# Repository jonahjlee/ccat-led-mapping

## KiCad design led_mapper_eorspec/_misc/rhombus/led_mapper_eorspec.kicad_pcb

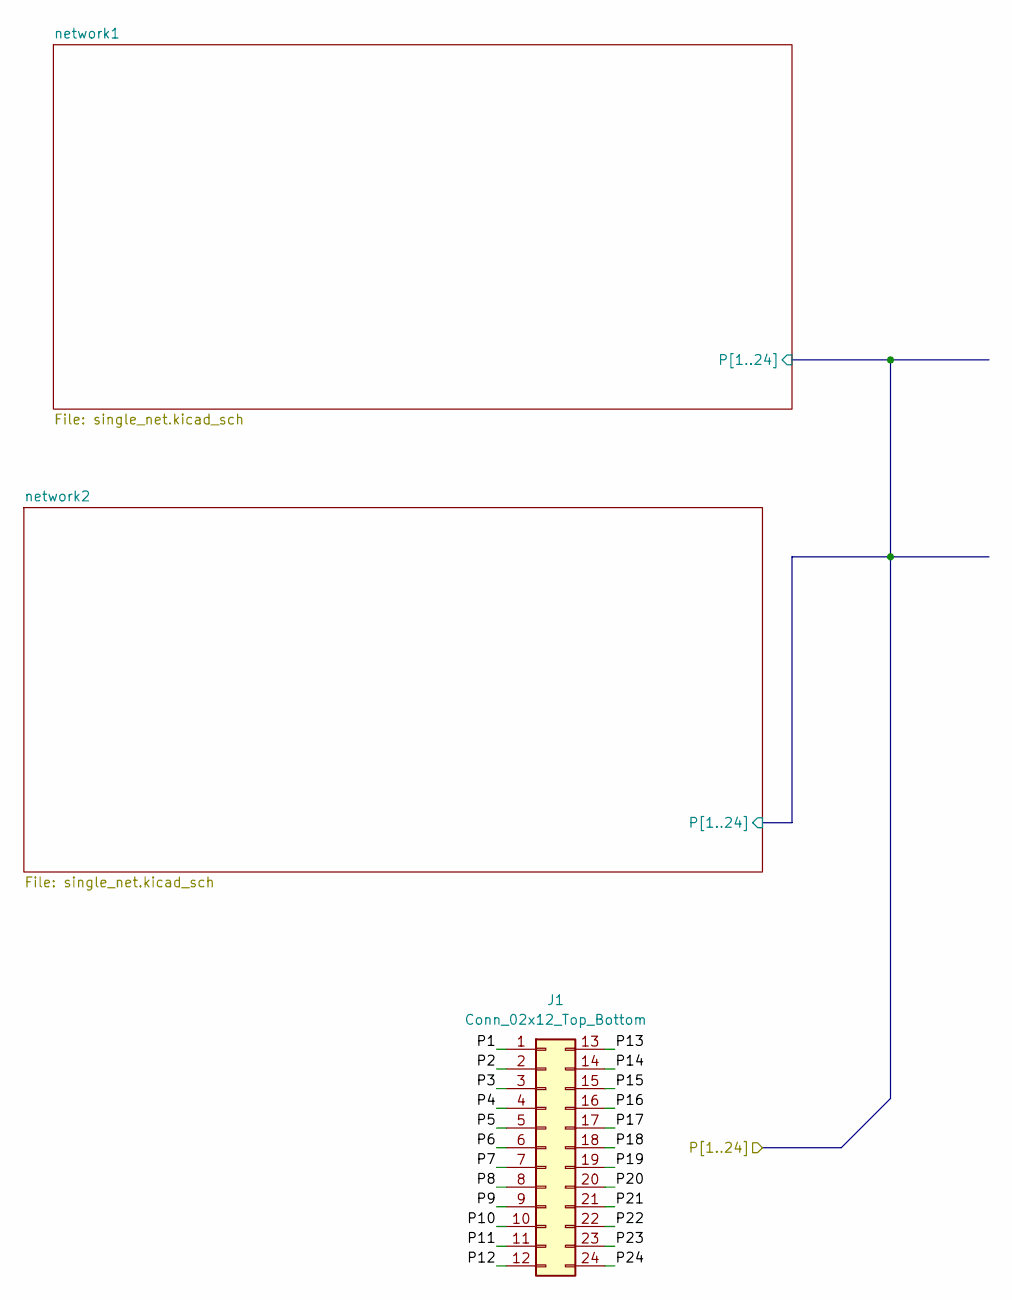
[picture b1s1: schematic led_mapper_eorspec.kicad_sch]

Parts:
J1: Conn_02x12_Top_Bottom; PinSocket_2x12_P2.54mm_Vertical_SMD_custom; LCSC Part # C19268781

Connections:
/P1: J1.1; also elsewhere on the board
/P2: J1.2; also elsewhere on the board
/P3: J1.3; also elsewhere on the board
/P4: J1.4; also elsewhere on the board
/P5: J1.5; also elsewhere on the board
/P6: J1.6; also elsewhere on the board
/P7: J1.7; also elsewhere on the board
/P8: J1.8; also elsewhere on the board
/P9: J1.9; also elsewhere on the board
/P10: J1.10; also elsewhere on the board
/P11: J1.11; also elsewhere on the board
/P12: J1.12; also elsewhere on the board
/P13: J1.13; also elsewhere on the board
/P14: J1.14; also elsewhere on the board
/P15: J1.15; also elsewhere on the board
/P16: J1.16; also elsewhere on the board
/P17: J1.17; also elsewhere on the board
/P18: J1.18; also elsewhere on the board
/P19: J1.19; also elsewhere on the board
/P20: J1.20; also elsewhere on the board
/P21: J1.21; also elsewhere on the board
/P22: J1.22; also elsewhere on the board
/P23: J1.23; also elsewhere on the board
/P24: J1.24; also elsewhere on the board

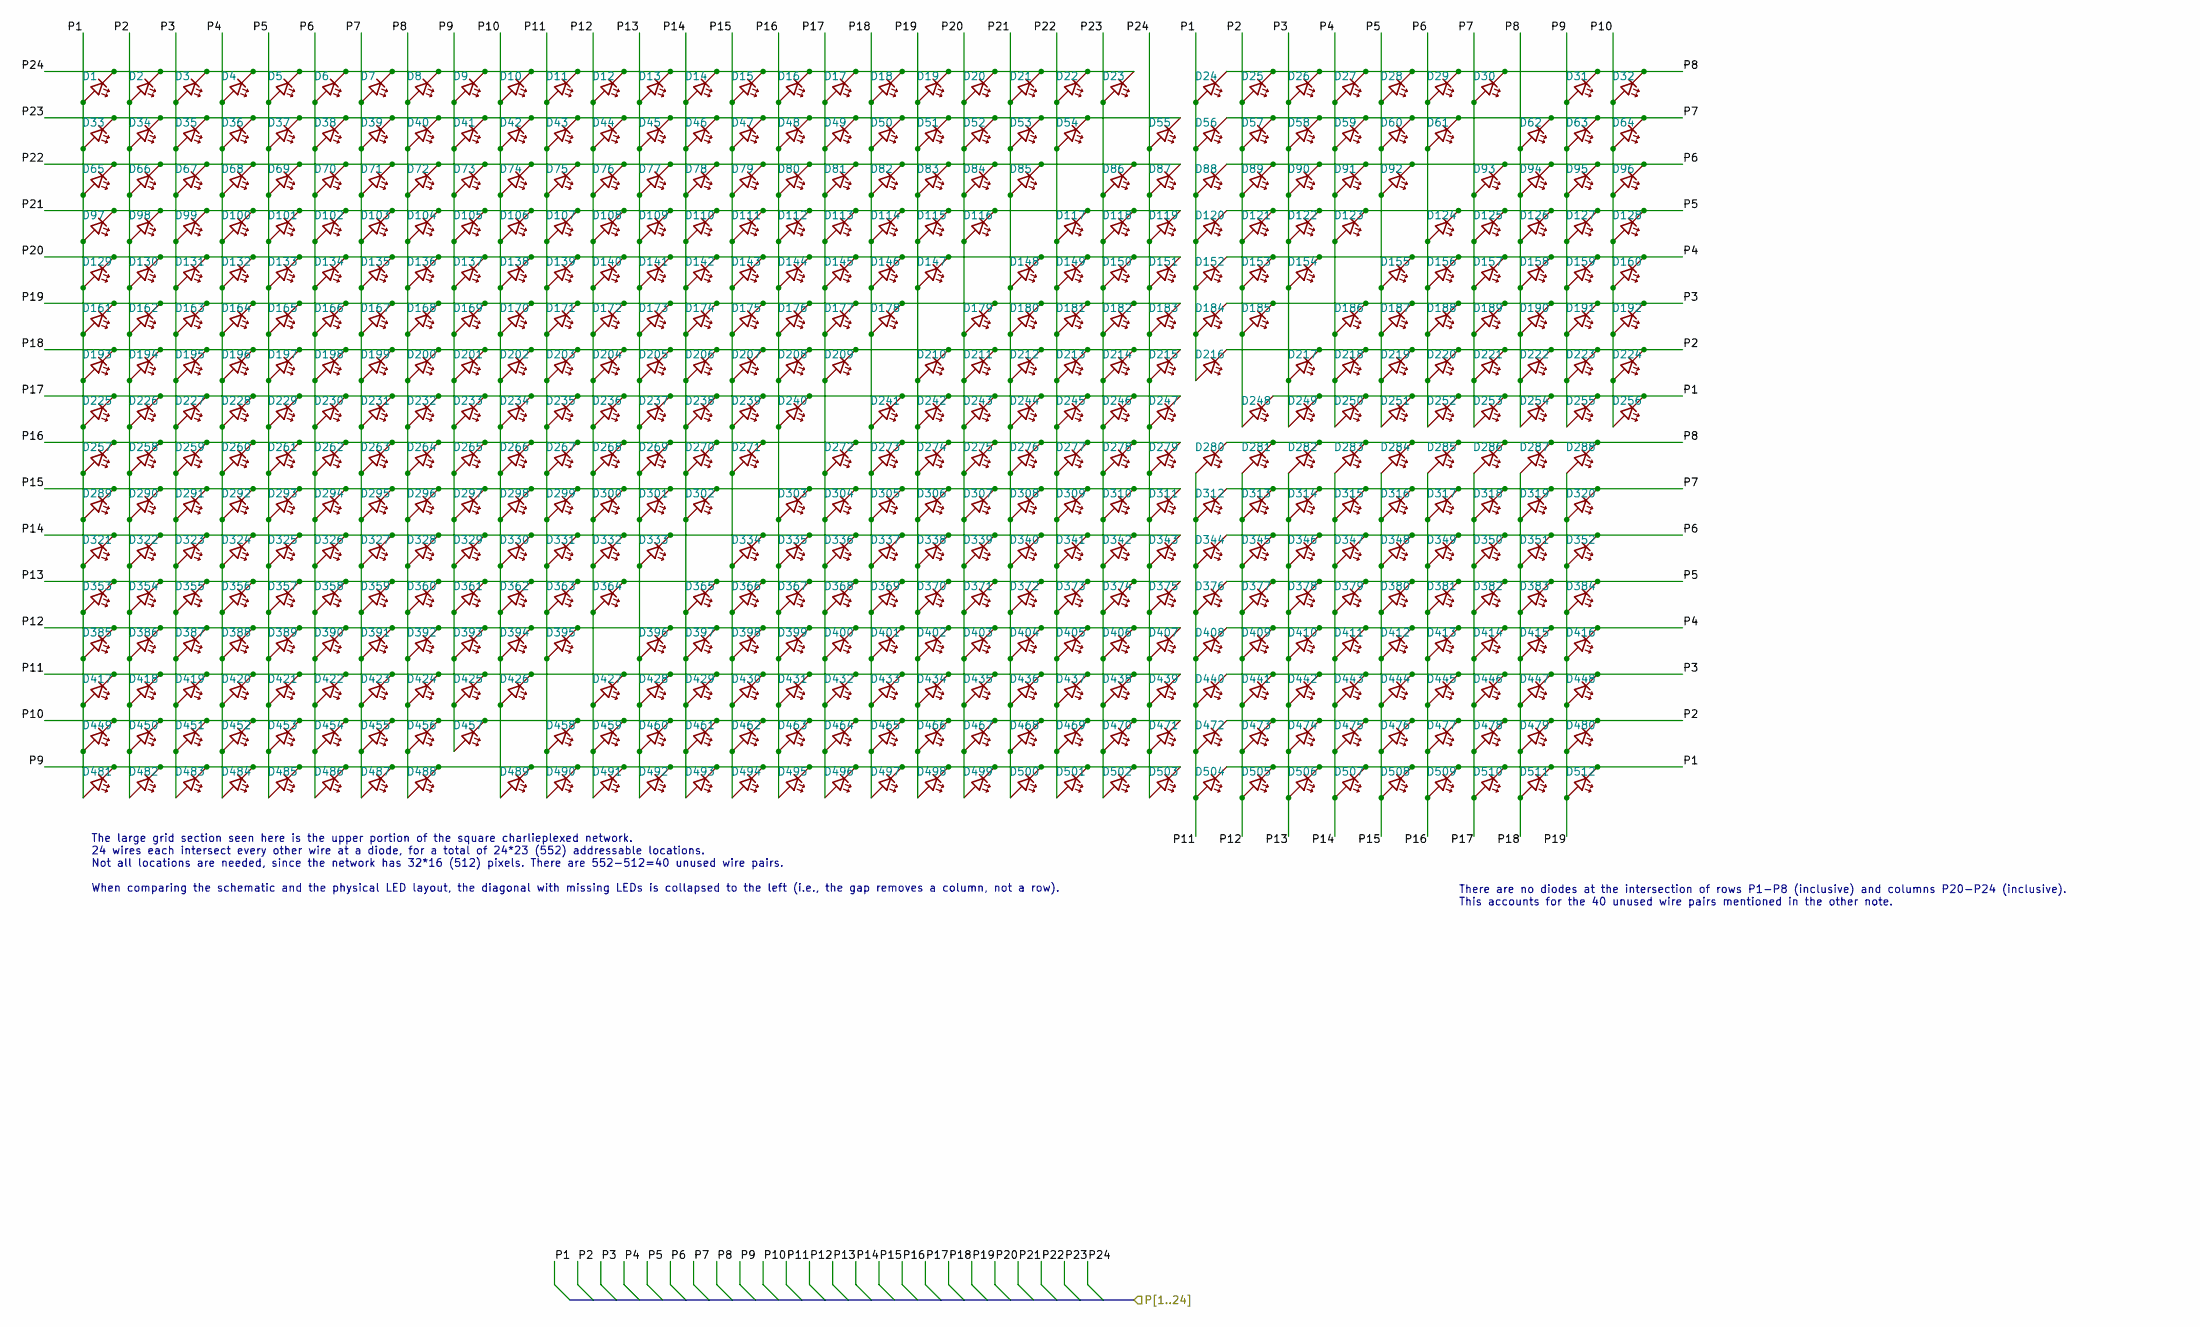
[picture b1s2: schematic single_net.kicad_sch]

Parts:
D1, D2, D3, D4, D5, D6, D7, D8, D9, D10, D11, D12, D13, D14, D15, D16, D17, D18, D19, D20, D21, D22, D23, D24, D25, D26, D27, D28, D29, D30, D31, D32, D33, D34, D35, D36, D37, D38, D39, D40, D41, D42, D43, D44, D45, D46, D47, D48, D49, D50, D51, D52, D53, D54, D55, D56, D57, D58, D59, D60, D61, D62, D63, D64, D65, D66, D67, D68, D69, D70, D71, D72, D73, D74, D75, D76, D77, D78, D79, D80, D81, D82, D83, D84, D85, D86, D87, D88, D89, D90, D91, D92, D93, D94, D95, D96, D97, D98, D99, D100, D101, D102, D103, D104, D105, D106, D107, D108, D109, D110, D111, D112, D113, D114, D115, D116, D117, D118, D119, D120, D121, D122, D123, D124, D125, D126, D127, D128, D129, D130, D131, D132, D133, D134, D135, D136, D137, D138, D139, D140, D141, D142, D143, D144, D145, D146, D147, D148, D149, D150, D151, D152, D153, D154, D155, D156, D157, D158, D159, D160, D161, D162, D163, D164, D165, D166, D167, D168, D169, D170, D171, D172, D173, D174, D175, D176, D177, D178, D179, D180, D181, D182, D183, D184, D185, D186, D187, D188, D189, D190, D191, D192, D193, D194, D195, D196, D197, D198, D199, D200, D201, D202, D203, D204, D205, D206, D207, D208, D209, D210, D211, D212, D213, D214, D215, D216, D217, D218, D219, D220, D221, D222, D223, D224, D225, D226, D227, D228, D229, D230, D231, D232, D233, D234, D235, D236, D237, D238, D239, D240, D241, D242, D243, D244, D245, D246, D247, D248, D249, D250, D251, D252, D253, D254, D255, D256, D257, D258, D259, D260, D261, D262, D263, D264, D265, D266, D267, D268, D269, D270, D271, D272, D273, D274, D275, D276, D277, D278, D279, D280, D281, D282, D283, D284, D285, D286, D287, D288, D289, D290, D291, D292, D293, D294, D295, D296, D297, D298, D299, D300, D301, D302, D303, D304, D305, D306, D307, D308, D309, D310, D311, D312, D313, D314, D315, D316, D317, D318, D319, D320, D321, D322, D323, D324, D325, D326, D327, D328, D329, D330, D331, D332, D333, D334, D335, D336, D337, D338, D339, D340, D341, D342, D343, D344, D345, D346, D347, D348, D349, D350, D351, D352, D353, D354, D355, D356, D357, D358, D359, D360, D361, D362, D363, D364, D365, D366, D367, D368, D369, D370, D371, D372, D373, D374, D375, D376, D377, D378, D379, D380, D381, D382, D383, D384, D385, D386, D387, D388, D389, D390, D391, D392, D393, D394, D395, D396, D397, D398, D399, D400, D401, D402, D403, D404, D405, D406, D407, D408, D409, D410, D411, D412, D413, D414, D415, D416, D417, D418, D419, D420, D421, D422, D423, D424, D425, D426, D427, D428, D429, D430, D431, D432, D433, D434, D435, D436, D437, D438, D439, D440, D441, D442, D443, D444, D445, D446, D447, D448, D449, D450, D451, D452, D453, D454, D455, D456, D457, D458, D459, D460, D461, D462, D463, D464, D465, D466, D467, D468, D469, D470, D471, D472, D473, D474, D475, D476, D477, D478, D479, D480, D481, D482, D483, D484, D485, D486, D487, D488, D489, D490, D491, D492, D493, D494, D495, D496, D497, D498, D499, D500, D501, D502, D503, D504, D505, D506, D507, D508, D509, D510, D511, D512: LED_45deg

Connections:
/P1: D1.2 (A), D24.2 (A), D33.2 (A), D56.2 (A), D65.2 (A), D88.2 (A), D97.2 (A), D120.2 (A), D129.2 (A), D152.2 (A), D161.2 (A), D184.2 (A), D193.2 (A), D216.2 (A), D225.2 (A), D248.1 (K), D249.1 (K), D250.1 (K), D251.1 (K), D252.1 (K), D253.1 (K), D254.1 (K), D255.1 (K), D256.1 (K), D257.2 (A), D289.2 (A), D321.2 (A), D353.2 (A), D385.2 (A), D417.2 (A), D449.2 (A), D481.2 (A), D504.1 (K), D505.1 (K), D506.1 (K), D507.1 (K), D508.1 (K), D509.1 (K), D510.1 (K), D511.1 (K), D512.1 (K); also elsewhere on the board
/P2: D2.2 (A), D25.2 (A), D34.2 (A), D57.2 (A), D66.2 (A), D89.2 (A), D98.2 (A), D121.2 (A), D130.2 (A), D153.2 (A), D162.2 (A), D185.2 (A), D194.2 (A), D216.1 (K), D217.1 (K), D218.1 (K), D219.1 (K), D220.1 (K), D221.1 (K), D222.1 (K), D223.1 (K), D224.1 (K), D226.2 (A), D248.2 (A), D258.2 (A), D290.2 (A), D322.2 (A), D354.2 (A), D386.2 (A), D418.2 (A), D450.2 (A), D472.1 (K), D473.1 (K), D474.1 (K), D475.1 (K), D476.1 (K), D477.1 (K), D478.1 (K), D479.1 (K), D480.1 (K), D482.2 (A); also elsewhere on the board
/P3: D3.2 (A), D26.2 (A), D35.2 (A), D58.2 (A), D67.2 (A), D90.2 (A), D99.2 (A), D122.2 (A), D131.2 (A), D154.2 (A), D163.2 (A), D184.1 (K), D185.1 (K), D186.1 (K), D187.1 (K), D188.1 (K), D189.1 (K), D190.1 (K), D191.1 (K), D192.1 (K), D195.2 (A), D217.2 (A), D227.2 (A), D249.2 (A), D259.2 (A), D291.2 (A), D323.2 (A), D355.2 (A), D387.2 (A), D419.2 (A), D440.1 (K), D441.1 (K), D442.1 (K), D443.1 (K), D444.1 (K), D445.1 (K), D446.1 (K), D447.1 (K), D448.1 (K), D451.2 (A), D483.2 (A); also elsewhere on the board
/P4: D4.2 (A), D27.2 (A), D36.2 (A), D59.2 (A), D68.2 (A), D91.2 (A), D100.2 (A), D123.2 (A), D132.2 (A), D152.1 (K), D153.1 (K), D154.1 (K), D155.1 (K), D156.1 (K), D157.1 (K), D158.1 (K), D159.1 (K), D160.1 (K), D164.2 (A), D186.2 (A), D196.2 (A), D218.2 (A), D228.2 (A), D250.2 (A), D260.2 (A), D292.2 (A), D324.2 (A), D356.2 (A), D388.2 (A), D408.1 (K), D409.1 (K), D410.1 (K), D411.1 (K), D412.1 (K), D413.1 (K), D414.1 (K), D415.1 (K), D416.1 (K), D420.2 (A), D452.2 (A), D484.2 (A); also elsewhere on the board
/P5: D5.2 (A), D28.2 (A), D37.2 (A), D60.2 (A), D69.2 (A), D92.2 (A), D101.2 (A), D120.1 (K), D121.1 (K), D122.1 (K), D123.1 (K), D124.1 (K), D125.1 (K), D126.1 (K), D127.1 (K), D128.1 (K), D133.2 (A), D155.2 (A), D165.2 (A), D187.2 (A), D197.2 (A), D219.2 (A), D229.2 (A), D251.2 (A), D261.2 (A), D293.2 (A), D325.2 (A), D357.2 (A), D376.1 (K), D377.1 (K), D378.1 (K), D379.1 (K), D380.1 (K), D381.1 (K), D382.1 (K), D383.1 (K), D384.1 (K), D389.2 (A), D421.2 (A), D453.2 (A), D485.2 (A); also elsewhere on the board
/P6: D6.2 (A), D29.2 (A), D38.2 (A), D61.2 (A), D70.2 (A), D88.1 (K), D89.1 (K), D90.1 (K), D91.1 (K), D92.1 (K), D93.1 (K), D94.1 (K), D95.1 (K), D96.1 (K), D102.2 (A), D124.2 (A), D134.2 (A), D156.2 (A), D166.2 (A), D188.2 (A), D198.2 (A), D220.2 (A), D230.2 (A), D252.2 (A), D262.2 (A), D294.2 (A), D326.2 (A), D344.1 (K), D345.1 (K), D346.1 (K), D347.1 (K), D348.1 (K), D349.1 (K), D350.1 (K), D351.1 (K), D352.1 (K), D358.2 (A), D390.2 (A), D422.2 (A), D454.2 (A), D486.2 (A); also elsewhere on the board
/P7: D7.2 (A), D30.2 (A), D39.2 (A), D56.1 (K), D57.1 (K), D58.1 (K), D59.1 (K), D60.1 (K), D61.1 (K), D62.1 (K), D63.1 (K), D64.1 (K), D71.2 (A), D93.2 (A), D103.2 (A), D125.2 (A), D135.2 (A), D157.2 (A), D167.2 (A), D189.2 (A), D199.2 (A), D221.2 (A), D231.2 (A), D253.2 (A), D263.2 (A), D295.2 (A), D312.1 (K), D313.1 (K), D314.1 (K), D315.1 (K), D316.1 (K), D317.1 (K), D318.1 (K), D319.1 (K), D320.1 (K), D327.2 (A), D359.2 (A), D391.2 (A), D423.2 (A), D455.2 (A), D487.2 (A); also elsewhere on the board
/P8: D8.2 (A), D24.1 (K), D25.1 (K), D26.1 (K), D27.1 (K), D28.1 (K), D29.1 (K), D30.1 (K), D31.1 (K), D32.1 (K), D40.2 (A), D62.2 (A), D72.2 (A), D94.2 (A), D104.2 (A), D126.2 (A), D136.2 (A), D158.2 (A), D168.2 (A), D190.2 (A), D200.2 (A), D222.2 (A), D232.2 (A), D254.2 (A), D264.2 (A), D280.1 (K), D281.1 (K), D282.1 (K), D283.1 (K), D284.1 (K), D285.1 (K), D286.1 (K), D287.1 (K), D288.1 (K), D296.2 (A), D328.2 (A), D360.2 (A), D392.2 (A), D424.2 (A), D456.2 (A), D488.2 (A); also elsewhere on the board
/P9: D9.2 (A), D31.2 (A), D41.2 (A), D63.2 (A), D73.2 (A), D95.2 (A), D105.2 (A), D127.2 (A), D137.2 (A), D159.2 (A), D169.2 (A), D191.2 (A), D201.2 (A), D223.2 (A), D233.2 (A), D255.2 (A), D265.2 (A), D297.2 (A), D329.2 (A), D361.2 (A), D393.2 (A), D425.2 (A), D457.2 (A), D481.1 (K), D482.1 (K), D483.1 (K), D484.1 (K), D485.1 (K), D486.1 (K), D487.1 (K), D488.1 (K), D489.1 (K), D490.1 (K), D491.1 (K), D492.1 (K), D493.1 (K), D494.1 (K), D495.1 (K), D496.1 (K), D497.1 (K), D498.1 (K), D499.1 (K), D500.1 (K), D501.1 (K), D502.1 (K), D503.1 (K); also elsewhere on the board
/P10: D10.2 (A), D32.2 (A), D42.2 (A), D64.2 (A), D74.2 (A), D96.2 (A), D106.2 (A), D128.2 (A), D138.2 (A), D160.2 (A), D170.2 (A), D192.2 (A), D202.2 (A), D224.2 (A), D234.2 (A), D256.2 (A), D266.2 (A), D298.2 (A), D330.2 (A), D362.2 (A), D394.2 (A), D426.2 (A), D449.1 (K), D450.1 (K), D451.1 (K), D452.1 (K), D453.1 (K), D454.1 (K), D455.1 (K), D456.1 (K), D457.1 (K), D458.1 (K), D459.1 (K), D460.1 (K), D461.1 (K), D462.1 (K), D463.1 (K), D464.1 (K), D465.1 (K), D466.1 (K), D467.1 (K), D468.1 (K), D469.1 (K), D470.1 (K), D471.1 (K), D489.2 (A); also elsewhere on the board
/P11: D11.2 (A), D43.2 (A), D75.2 (A), D107.2 (A), D139.2 (A), D171.2 (A), D203.2 (A), D235.2 (A), D267.2 (A), D280.2 (A), D299.2 (A), D312.2 (A), D331.2 (A), D344.2 (A), D363.2 (A), D376.2 (A), D395.2 (A), D408.2 (A), D417.1 (K), D418.1 (K), D419.1 (K), D420.1 (K), D421.1 (K), D422.1 (K), D423.1 (K), D424.1 (K), D425.1 (K), D426.1 (K), D427.1 (K), D428.1 (K), D429.1 (K), D430.1 (K), D431.1 (K), D432.1 (K), D433.1 (K), D434.1 (K), D435.1 (K), D436.1 (K), D437.1 (K), D438.1 (K), D439.1 (K), D440.2 (A), D458.2 (A), D472.2 (A), D490.2 (A), D504.2 (A); also elsewhere on the board
/P12: D12.2 (A), D44.2 (A), D76.2 (A), D108.2 (A), D140.2 (A), D172.2 (A), D204.2 (A), D236.2 (A), D268.2 (A), D281.2 (A), D300.2 (A), D313.2 (A), D332.2 (A), D345.2 (A), D364.2 (A), D377.2 (A), D385.1 (K), D386.1 (K), D387.1 (K), D388.1 (K), D389.1 (K), D390.1 (K), D391.1 (K), D392.1 (K), D393.1 (K), D394.1 (K), D395.1 (K), D396.1 (K), D397.1 (K), D398.1 (K), D399.1 (K), D400.1 (K), D401.1 (K), D402.1 (K), D403.1 (K), D404.1 (K), D405.1 (K), D406.1 (K), D407.1 (K), D409.2 (A), D427.2 (A), D441.2 (A), D459.2 (A), D473.2 (A), D491.2 (A), D505.2 (A); also elsewhere on the board
/P13: D13.2 (A), D45.2 (A), D77.2 (A), D109.2 (A), D141.2 (A), D173.2 (A), D205.2 (A), D237.2 (A), D269.2 (A), D282.2 (A), D301.2 (A), D314.2 (A), D333.2 (A), D346.2 (A), D353.1 (K), D354.1 (K), D355.1 (K), D356.1 (K), D357.1 (K), D358.1 (K), D359.1 (K), D360.1 (K), D361.1 (K), D362.1 (K), D363.1 (K), D364.1 (K), D365.1 (K), D366.1 (K), D367.1 (K), D368.1 (K), D369.1 (K), D370.1 (K), D371.1 (K), D372.1 (K), D373.1 (K), D374.1 (K), D375.1 (K), D378.2 (A), D396.2 (A), D410.2 (A), D428.2 (A), D442.2 (A), D460.2 (A), D474.2 (A), D492.2 (A), D506.2 (A); also elsewhere on the board
/P14: D14.2 (A), D46.2 (A), D78.2 (A), D110.2 (A), D142.2 (A), D174.2 (A), D206.2 (A), D238.2 (A), D270.2 (A), D283.2 (A), D302.2 (A), D315.2 (A), D321.1 (K), D322.1 (K), D323.1 (K), D324.1 (K), D325.1 (K), D326.1 (K), D327.1 (K), D328.1 (K), D329.1 (K), D330.1 (K), D331.1 (K), D332.1 (K), D333.1 (K), D334.1 (K), D335.1 (K), D336.1 (K), D337.1 (K), D338.1 (K), D339.1 (K), D340.1 (K), D341.1 (K), D342.1 (K), D343.1 (K), D347.2 (A), D365.2 (A), D379.2 (A), D397.2 (A), D411.2 (A), D429.2 (A), D443.2 (A), D461.2 (A), D475.2 (A), D493.2 (A), D507.2 (A); also elsewhere on the board
/P15: D15.2 (A), D47.2 (A), D79.2 (A), D111.2 (A), D143.2 (A), D175.2 (A), D207.2 (A), D239.2 (A), D271.2 (A), D284.2 (A), D289.1 (K), D290.1 (K), D291.1 (K), D292.1 (K), D293.1 (K), D294.1 (K), D295.1 (K), D296.1 (K), D297.1 (K), D298.1 (K), D299.1 (K), D300.1 (K), D301.1 (K), D302.1 (K), D303.1 (K), D304.1 (K), D305.1 (K), D306.1 (K), D307.1 (K), D308.1 (K), D309.1 (K), D310.1 (K), D311.1 (K), D316.2 (A), D334.2 (A), D348.2 (A), D366.2 (A), D380.2 (A), D398.2 (A), D412.2 (A), D430.2 (A), D444.2 (A), D462.2 (A), D476.2 (A), D494.2 (A), D508.2 (A); also elsewhere on the board
/P16: D16.2 (A), D48.2 (A), D80.2 (A), D112.2 (A), D144.2 (A), D176.2 (A), D208.2 (A), D240.2 (A), D257.1 (K), D258.1 (K), D259.1 (K), D260.1 (K), D261.1 (K), D262.1 (K), D263.1 (K), D264.1 (K), D265.1 (K), D266.1 (K), D267.1 (K), D268.1 (K), D269.1 (K), D270.1 (K), D271.1 (K), D272.1 (K), D273.1 (K), D274.1 (K), D275.1 (K), D276.1 (K), D277.1 (K), D278.1 (K), D279.1 (K), D285.2 (A), D303.2 (A), D317.2 (A), D335.2 (A), D349.2 (A), D367.2 (A), D381.2 (A), D399.2 (A), D413.2 (A), D431.2 (A), D445.2 (A), D463.2 (A), D477.2 (A), D495.2 (A), D509.2 (A); also elsewhere on the board
/P17: D17.2 (A), D49.2 (A), D81.2 (A), D113.2 (A), D145.2 (A), D177.2 (A), D209.2 (A), D225.1 (K), D226.1 (K), D227.1 (K), D228.1 (K), D229.1 (K), D230.1 (K), D231.1 (K), D232.1 (K), D233.1 (K), D234.1 (K), D235.1 (K), D236.1 (K), D237.1 (K), D238.1 (K), D239.1 (K), D240.1 (K), D241.1 (K), D242.1 (K), D243.1 (K), D244.1 (K), D245.1 (K), D246.1 (K), D247.1 (K), D272.2 (A), D286.2 (A), D304.2 (A), D318.2 (A), D336.2 (A), D350.2 (A), D368.2 (A), D382.2 (A), D400.2 (A), D414.2 (A), D432.2 (A), D446.2 (A), D464.2 (A), D478.2 (A), D496.2 (A), D510.2 (A); also elsewhere on the board
/P18: D18.2 (A), D50.2 (A), D82.2 (A), D114.2 (A), D146.2 (A), D178.2 (A), D193.1 (K), D194.1 (K), D195.1 (K), D196.1 (K), D197.1 (K), D198.1 (K), D199.1 (K), D200.1 (K), D201.1 (K), D202.1 (K), D203.1 (K), D204.1 (K), D205.1 (K), D206.1 (K), D207.1 (K), D208.1 (K), D209.1 (K), D210.1 (K), D211.1 (K), D212.1 (K), D213.1 (K), D214.1 (K), D215.1 (K), D241.2 (A), D273.2 (A), D287.2 (A), D305.2 (A), D319.2 (A), D337.2 (A), D351.2 (A), D369.2 (A), D383.2 (A), D401.2 (A), D415.2 (A), D433.2 (A), D447.2 (A), D465.2 (A), D479.2 (A), D497.2 (A), D511.2 (A); also elsewhere on the board
/P19: D19.2 (A), D51.2 (A), D83.2 (A), D115.2 (A), D147.2 (A), D161.1 (K), D162.1 (K), D163.1 (K), D164.1 (K), D165.1 (K), D166.1 (K), D167.1 (K), D168.1 (K), D169.1 (K), D170.1 (K), D171.1 (K), D172.1 (K), D173.1 (K), D174.1 (K), D175.1 (K), D176.1 (K), D177.1 (K), D178.1 (K), D179.1 (K), D180.1 (K), D181.1 (K), D182.1 (K), D183.1 (K), D210.2 (A), D242.2 (A), D274.2 (A), D288.2 (A), D306.2 (A), D320.2 (A), D338.2 (A), D352.2 (A), D370.2 (A), D384.2 (A), D402.2 (A), D416.2 (A), D434.2 (A), D448.2 (A), D466.2 (A), D480.2 (A), D498.2 (A), D512.2 (A); also elsewhere on the board
/P20: D20.2 (A), D52.2 (A), D84.2 (A), D116.2 (A), D129.1 (K), D130.1 (K), D131.1 (K), D132.1 (K), D133.1 (K), D134.1 (K), D135.1 (K), D136.1 (K), D137.1 (K), D138.1 (K), D139.1 (K), D140.1 (K), D141.1 (K), D142.1 (K), D143.1 (K), D144.1 (K), D145.1 (K), D146.1 (K), D147.1 (K), D148.1 (K), D149.1 (K), D150.1 (K), D151.1 (K), D179.2 (A), D211.2 (A), D243.2 (A), D275.2 (A), D307.2 (A), D339.2 (A), D371.2 (A), D403.2 (A), D435.2 (A), D467.2 (A), D499.2 (A); also elsewhere on the board
/P21: D21.2 (A), D53.2 (A), D85.2 (A), D97.1 (K), D98.1 (K), D99.1 (K), D100.1 (K), D101.1 (K), D102.1 (K), D103.1 (K), D104.1 (K), D105.1 (K), D106.1 (K), D107.1 (K), D108.1 (K), D109.1 (K), D110.1 (K), D111.1 (K), D112.1 (K), D113.1 (K), D114.1 (K), D115.1 (K), D116.1 (K), D117.1 (K), D118.1 (K), D119.1 (K), D148.2 (A), D180.2 (A), D212.2 (A), D244.2 (A), D276.2 (A), D308.2 (A), D340.2 (A), D372.2 (A), D404.2 (A), D436.2 (A), D468.2 (A), D500.2 (A); also elsewhere on the board
/P22: D22.2 (A), D54.2 (A), D65.1 (K), D66.1 (K), D67.1 (K), D68.1 (K), D69.1 (K), D70.1 (K), D71.1 (K), D72.1 (K), D73.1 (K), D74.1 (K), D75.1 (K), D76.1 (K), D77.1 (K), D78.1 (K), D79.1 (K), D80.1 (K), D81.1 (K), D82.1 (K), D83.1 (K), D84.1 (K), D85.1 (K), D86.1 (K), D87.1 (K), D117.2 (A), D149.2 (A), D181.2 (A), D213.2 (A), D245.2 (A), D277.2 (A), D309.2 (A), D341.2 (A), D373.2 (A), D405.2 (A), D437.2 (A), D469.2 (A), D501.2 (A); also elsewhere on the board
/P23: D23.2 (A), D33.1 (K), D34.1 (K), D35.1 (K), D36.1 (K), D37.1 (K), D38.1 (K), D39.1 (K), D40.1 (K), D41.1 (K), D42.1 (K), D43.1 (K), D44.1 (K), D45.1 (K), D46.1 (K), D47.1 (K), D48.1 (K), D49.1 (K), D50.1 (K), D51.1 (K), D52.1 (K), D53.1 (K), D54.1 (K), D55.1 (K), D86.2 (A), D118.2 (A), D150.2 (A), D182.2 (A), D214.2 (A), D246.2 (A), D278.2 (A), D310.2 (A), D342.2 (A), D374.2 (A), D406.2 (A), D438.2 (A), D470.2 (A), D502.2 (A); also elsewhere on the board
/P24: D1.1 (K), D2.1 (K), D3.1 (K), D4.1 (K), D5.1 (K), D6.1 (K), D7.1 (K), D8.1 (K), D9.1 (K), D10.1 (K), D11.1 (K), D12.1 (K), D13.1 (K), D14.1 (K), D15.1 (K), D16.1 (K), D17.1 (K), D18.1 (K), D19.1 (K), D20.1 (K), D21.1 (K), D22.1 (K), D23.1 (K), D55.2 (A), D87.2 (A), D119.2 (A), D151.2 (A), D183.2 (A), D215.2 (A), D247.2 (A), D279.2 (A), D311.2 (A), D343.2 (A), D375.2 (A), D407.2 (A), D439.2 (A), D471.2 (A), D503.2 (A); also elsewhere on the board

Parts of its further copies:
D513, D514, D515, D516, D517, D518, D519, D520, D521, D522, D523, D524, D525, D526, D527, D528, D529, D530, D531, D532, D533, D534, D535, D536, D537, D538, D539, D540, D541, D542, D543, D544, D545, D546, D547, D548, D549, D550, D551, D552, D553, D554, D555, D556, D557, D558, D559, D560, D561, D562, D563, D564, D565, D566, D567, D568, D569, D570, D571, D572, D573, D574, D575, D576, D577, D578, D579, D580, D581, D582, D583, D584, D585, D586, D587, D588, D589, D590, D591, D592, D593, D594, D595, D596, D597, D598, D599, D600, D601, D602, D603, D604, D605, D606, D607, D608, D609, D610, D611, D612, D613, D614, D615, D616, D617, D618, D619, D620, D621, D622, D623, D624, D625, D626, D627, D628, D629, D630, D631, D632, D633, D634, D635, D636, D637, D638, D639, D640, D641, D642, D643, D644, D645, D646, D647, D648, D649, D650, D651, D652, D653, D654, D655, D656, D657, D658, D659, D660, D661, D662, D663, D664, D665, D666, D667, D668, D669, D670, D671, D672, D673, D674, D675, D676, D677, D678, D679, D680, D681, D682, D683, D684, D685, D686, D687, D688, D689, D690, D691, D692, D693, D694, D695, D696, D697, D698, D699, D700, D701, D702, D703, D704, D705, D706, D707, D708, D709, D710, D711, D712, D713, D714, D715, D716, D717, D718, D719, D720, D721, D722, D723, D724, D725, D726, D727, D728, D729, D730, D731, D732, D733, D734, D735, D736, D737, D738, D739, D740, D741, D742, D743, D744, D745, D746, D747, D748, D749, D750, D751, D752, D753, D754, D755, D756, D757, D758, D759, D760, D761, D762, D763, D764, D765, D766, D767, D768, D769, D770, D771, D772, D773, D774, D775, D776, D777, D778, D779, D780, D781, D782, D783, D784, D785, D786, D787, D788, D789, D790, D791, D792, D793, D794, D795, D796, D797, D798, D799, D800, D801, D802, D803, D804, D805, D806, D807, D808, D809, D810, D811, D812, D813, D814, D815, D816, D817, D818, D819, D820, D821, D822, D823, D824, D825, D826, D827, D828, D829, D830, D831, D832, D833, D834, D835, D836, D837, D838, D839, D840, D841, D842, D843, D844, D845, D846, D847, D848, D849, D850, D851, D852, D853, D854, D855, D856, D857, D858, D859, D860, D861, D862, D863, D864, D865, D866, D867, D868, D869, D870, D871, D872, D873, D874, D875, D876, D877, D878, D879, D880, D881, D882, D883, D884, D885, D886, D887, D888, D889, D890, D891, D892, D893, D894, D895, D896, D897, D898, D899, D900, D901, D902, D903, D904, D905, D906, D907, D908, D909, D910, D911, D912, D913, D914, D915, D916, D917, D918, D919, D920, D921, D922, D923, D924, D925, D926, D927, D928, D929, D930, D931, D932, D933, D934, D935, D936, D937, D938, D939, D940, D941, D942, D943, D944, D945, D946, D947, D948, D949, D950, D951, D952, D953, D954, D955, D956, D957, D958, D959, D960, D961, D962, D963, D964, D965, D966, D967, D968, D969, D970, D971, D972, D973, D974, D975, D976, D977, D978, D979, D980, D981, D982, D983, D984, D985, D986, D987, D988, D989, D990, D991, D992, D993, D994, D995, D996, D997, D998, D999, D1000, D1001, D1002, D1003, D1004, D1005, D1006, D1007, D1008, D1009, D1010, D1011, D1012, D1013, D1014, D1015, D1016, D1017, D1018, D1019, D1020, D1021, D1022, D1023, D1024: LED_45deg

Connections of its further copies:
/P1: D513.2 (A), D536.2 (A), D545.2 (A), D568.2 (A), D577.2 (A), D600.2 (A), D609.2 (A), D632.2 (A), D641.2 (A), D664.2 (A), D673.2 (A), D696.2 (A), D705.2 (A), D728.2 (A), D737.2 (A), D760.1 (K), D761.1 (K), D762.1 (K), D763.1 (K), D764.1 (K), D765.1 (K), D766.1 (K), D767.1 (K), D768.1 (K), D769.2 (A), D801.2 (A), D833.2 (A), D865.2 (A), D897.2 (A), D929.2 (A), D961.2 (A), D993.2 (A), D1016.1 (K), D1017.1 (K), D1018.1 (K), D1019.1 (K), D1020.1 (K), D1021.1 (K), D1022.1 (K), D1023.1 (K), D1024.1 (K); also elsewhere on the board
/P2: D514.2 (A), D537.2 (A), D546.2 (A), D569.2 (A), D578.2 (A), D601.2 (A), D610.2 (A), D633.2 (A), D642.2 (A), D665.2 (A), D674.2 (A), D697.2 (A), D706.2 (A), D728.1 (K), D729.1 (K), D730.1 (K), D731.1 (K), D732.1 (K), D733.1 (K), D734.1 (K), D735.1 (K), D736.1 (K), D738.2 (A), D760.2 (A), D770.2 (A), D802.2 (A), D834.2 (A), D866.2 (A), D898.2 (A), D930.2 (A), D962.2 (A), D984.1 (K), D985.1 (K), D986.1 (K), D987.1 (K), D988.1 (K), D989.1 (K), D990.1 (K), D991.1 (K), D992.1 (K), D994.2 (A); also elsewhere on the board
/P3: D515.2 (A), D538.2 (A), D547.2 (A), D570.2 (A), D579.2 (A), D602.2 (A), D611.2 (A), D634.2 (A), D643.2 (A), D666.2 (A), D675.2 (A), D696.1 (K), D697.1 (K), D698.1 (K), D699.1 (K), D700.1 (K), D701.1 (K), D702.1 (K), D703.1 (K), D704.1 (K), D707.2 (A), D729.2 (A), D739.2 (A), D761.2 (A), D771.2 (A), D803.2 (A), D835.2 (A), D867.2 (A), D899.2 (A), D931.2 (A), D952.1 (K), D953.1 (K), D954.1 (K), D955.1 (K), D956.1 (K), D957.1 (K), D958.1 (K), D959.1 (K), D960.1 (K), D963.2 (A), D995.2 (A); also elsewhere on the board
/P4: D516.2 (A), D539.2 (A), D548.2 (A), D571.2 (A), D580.2 (A), D603.2 (A), D612.2 (A), D635.2 (A), D644.2 (A), D664.1 (K), D665.1 (K), D666.1 (K), D667.1 (K), D668.1 (K), D669.1 (K), D670.1 (K), D671.1 (K), D672.1 (K), D676.2 (A), D698.2 (A), D708.2 (A), D730.2 (A), D740.2 (A), D762.2 (A), D772.2 (A), D804.2 (A), D836.2 (A), D868.2 (A), D900.2 (A), D920.1 (K), D921.1 (K), D922.1 (K), D923.1 (K), D924.1 (K), D925.1 (K), D926.1 (K), D927.1 (K), D928.1 (K), D932.2 (A), D964.2 (A), D996.2 (A); also elsewhere on the board
/P5: D517.2 (A), D540.2 (A), D549.2 (A), D572.2 (A), D581.2 (A), D604.2 (A), D613.2 (A), D632.1 (K), D633.1 (K), D634.1 (K), D635.1 (K), D636.1 (K), D637.1 (K), D638.1 (K), D639.1 (K), D640.1 (K), D645.2 (A), D667.2 (A), D677.2 (A), D699.2 (A), D709.2 (A), D731.2 (A), D741.2 (A), D763.2 (A), D773.2 (A), D805.2 (A), D837.2 (A), D869.2 (A), D888.1 (K), D889.1 (K), D890.1 (K), D891.1 (K), D892.1 (K), D893.1 (K), D894.1 (K), D895.1 (K), D896.1 (K), D901.2 (A), D933.2 (A), D965.2 (A), D997.2 (A); also elsewhere on the board
/P6: D518.2 (A), D541.2 (A), D550.2 (A), D573.2 (A), D582.2 (A), D600.1 (K), D601.1 (K), D602.1 (K), D603.1 (K), D604.1 (K), D605.1 (K), D606.1 (K), D607.1 (K), D608.1 (K), D614.2 (A), D636.2 (A), D646.2 (A), D668.2 (A), D678.2 (A), D700.2 (A), D710.2 (A), D732.2 (A), D742.2 (A), D764.2 (A), D774.2 (A), D806.2 (A), D838.2 (A), D856.1 (K), D857.1 (K), D858.1 (K), D859.1 (K), D860.1 (K), D861.1 (K), D862.1 (K), D863.1 (K), D864.1 (K), D870.2 (A), D902.2 (A), D934.2 (A), D966.2 (A), D998.2 (A); also elsewhere on the board
/P7: D519.2 (A), D542.2 (A), D551.2 (A), D568.1 (K), D569.1 (K), D570.1 (K), D571.1 (K), D572.1 (K), D573.1 (K), D574.1 (K), D575.1 (K), D576.1 (K), D583.2 (A), D605.2 (A), D615.2 (A), D637.2 (A), D647.2 (A), D669.2 (A), D679.2 (A), D701.2 (A), D711.2 (A), D733.2 (A), D743.2 (A), D765.2 (A), D775.2 (A), D807.2 (A), D824.1 (K), D825.1 (K), D826.1 (K), D827.1 (K), D828.1 (K), D829.1 (K), D830.1 (K), D831.1 (K), D832.1 (K), D839.2 (A), D871.2 (A), D903.2 (A), D935.2 (A), D967.2 (A), D999.2 (A); also elsewhere on the board
/P8: D520.2 (A), D536.1 (K), D537.1 (K), D538.1 (K), D539.1 (K), D540.1 (K), D541.1 (K), D542.1 (K), D543.1 (K), D544.1 (K), D552.2 (A), D574.2 (A), D584.2 (A), D606.2 (A), D616.2 (A), D638.2 (A), D648.2 (A), D670.2 (A), D680.2 (A), D702.2 (A), D712.2 (A), D734.2 (A), D744.2 (A), D766.2 (A), D776.2 (A), D792.1 (K), D793.1 (K), D794.1 (K), D795.1 (K), D796.1 (K), D797.1 (K), D798.1 (K), D799.1 (K), D800.1 (K), D808.2 (A), D840.2 (A), D872.2 (A), D904.2 (A), D936.2 (A), D968.2 (A), D1000.2 (A); also elsewhere on the board
/P9: D521.2 (A), D543.2 (A), D553.2 (A), D575.2 (A), D585.2 (A), D607.2 (A), D617.2 (A), D639.2 (A), D649.2 (A), D671.2 (A), D681.2 (A), D703.2 (A), D713.2 (A), D735.2 (A), D745.2 (A), D767.2 (A), D777.2 (A), D809.2 (A), D841.2 (A), D873.2 (A), D905.2 (A), D937.2 (A), D969.2 (A), D993.1 (K), D994.1 (K), D995.1 (K), D996.1 (K), D997.1 (K), D998.1 (K), D999.1 (K), D1000.1 (K), D1001.1 (K), D1002.1 (K), D1003.1 (K), D1004.1 (K), D1005.1 (K), D1006.1 (K), D1007.1 (K), D1008.1 (K), D1009.1 (K), D1010.1 (K), D1011.1 (K), D1012.1 (K), D1013.1 (K), D1014.1 (K), D1015.1 (K); also elsewhere on the board
/P10: D522.2 (A), D544.2 (A), D554.2 (A), D576.2 (A), D586.2 (A), D608.2 (A), D618.2 (A), D640.2 (A), D650.2 (A), D672.2 (A), D682.2 (A), D704.2 (A), D714.2 (A), D736.2 (A), D746.2 (A), D768.2 (A), D778.2 (A), D810.2 (A), D842.2 (A), D874.2 (A), D906.2 (A), D938.2 (A), D961.1 (K), D962.1 (K), D963.1 (K), D964.1 (K), D965.1 (K), D966.1 (K), D967.1 (K), D968.1 (K), D969.1 (K), D970.1 (K), D971.1 (K), D972.1 (K), D973.1 (K), D974.1 (K), D975.1 (K), D976.1 (K), D977.1 (K), D978.1 (K), D979.1 (K), D980.1 (K), D981.1 (K), D982.1 (K), D983.1 (K), D1001.2 (A); also elsewhere on the board
/P11: D523.2 (A), D555.2 (A), D587.2 (A), D619.2 (A), D651.2 (A), D683.2 (A), D715.2 (A), D747.2 (A), D779.2 (A), D792.2 (A), D811.2 (A), D824.2 (A), D843.2 (A), D856.2 (A), D875.2 (A), D888.2 (A), D907.2 (A), D920.2 (A), D929.1 (K), D930.1 (K), D931.1 (K), D932.1 (K), D933.1 (K), D934.1 (K), D935.1 (K), D936.1 (K), D937.1 (K), D938.1 (K), D939.1 (K), D940.1 (K), D941.1 (K), D942.1 (K), D943.1 (K), D944.1 (K), D945.1 (K), D946.1 (K), D947.1 (K), D948.1 (K), D949.1 (K), D950.1 (K), D951.1 (K), D952.2 (A), D970.2 (A), D984.2 (A), D1002.2 (A), D1016.2 (A); also elsewhere on the board
/P12: D524.2 (A), D556.2 (A), D588.2 (A), D620.2 (A), D652.2 (A), D684.2 (A), D716.2 (A), D748.2 (A), D780.2 (A), D793.2 (A), D812.2 (A), D825.2 (A), D844.2 (A), D857.2 (A), D876.2 (A), D889.2 (A), D897.1 (K), D898.1 (K), D899.1 (K), D900.1 (K), D901.1 (K), D902.1 (K), D903.1 (K), D904.1 (K), D905.1 (K), D906.1 (K), D907.1 (K), D908.1 (K), D909.1 (K), D910.1 (K), D911.1 (K), D912.1 (K), D913.1 (K), D914.1 (K), D915.1 (K), D916.1 (K), D917.1 (K), D918.1 (K), D919.1 (K), D921.2 (A), D939.2 (A), D953.2 (A), D971.2 (A), D985.2 (A), D1003.2 (A), D1017.2 (A); also elsewhere on the board
/P13: D525.2 (A), D557.2 (A), D589.2 (A), D621.2 (A), D653.2 (A), D685.2 (A), D717.2 (A), D749.2 (A), D781.2 (A), D794.2 (A), D813.2 (A), D826.2 (A), D845.2 (A), D858.2 (A), D865.1 (K), D866.1 (K), D867.1 (K), D868.1 (K), D869.1 (K), D870.1 (K), D871.1 (K), D872.1 (K), D873.1 (K), D874.1 (K), D875.1 (K), D876.1 (K), D877.1 (K), D878.1 (K), D879.1 (K), D880.1 (K), D881.1 (K), D882.1 (K), D883.1 (K), D884.1 (K), D885.1 (K), D886.1 (K), D887.1 (K), D890.2 (A), D908.2 (A), D922.2 (A), D940.2 (A), D954.2 (A), D972.2 (A), D986.2 (A), D1004.2 (A), D1018.2 (A); also elsewhere on the board
/P14: D526.2 (A), D558.2 (A), D590.2 (A), D622.2 (A), D654.2 (A), D686.2 (A), D718.2 (A), D750.2 (A), D782.2 (A), D795.2 (A), D814.2 (A), D827.2 (A), D833.1 (K), D834.1 (K), D835.1 (K), D836.1 (K), D837.1 (K), D838.1 (K), D839.1 (K), D840.1 (K), D841.1 (K), D842.1 (K), D843.1 (K), D844.1 (K), D845.1 (K), D846.1 (K), D847.1 (K), D848.1 (K), D849.1 (K), D850.1 (K), D851.1 (K), D852.1 (K), D853.1 (K), D854.1 (K), D855.1 (K), D859.2 (A), D877.2 (A), D891.2 (A), D909.2 (A), D923.2 (A), D941.2 (A), D955.2 (A), D973.2 (A), D987.2 (A), D1005.2 (A), D1019.2 (A); also elsewhere on the board
/P15: D527.2 (A), D559.2 (A), D591.2 (A), D623.2 (A), D655.2 (A), D687.2 (A), D719.2 (A), D751.2 (A), D783.2 (A), D796.2 (A), D801.1 (K), D802.1 (K), D803.1 (K), D804.1 (K), D805.1 (K), D806.1 (K), D807.1 (K), D808.1 (K), D809.1 (K), D810.1 (K), D811.1 (K), D812.1 (K), D813.1 (K), D814.1 (K), D815.1 (K), D816.1 (K), D817.1 (K), D818.1 (K), D819.1 (K), D820.1 (K), D821.1 (K), D822.1 (K), D823.1 (K), D828.2 (A), D846.2 (A), D860.2 (A), D878.2 (A), D892.2 (A), D910.2 (A), D924.2 (A), D942.2 (A), D956.2 (A), D974.2 (A), D988.2 (A), D1006.2 (A), D1020.2 (A); also elsewhere on the board
/P16: D528.2 (A), D560.2 (A), D592.2 (A), D624.2 (A), D656.2 (A), D688.2 (A), D720.2 (A), D752.2 (A), D769.1 (K), D770.1 (K), D771.1 (K), D772.1 (K), D773.1 (K), D774.1 (K), D775.1 (K), D776.1 (K), D777.1 (K), D778.1 (K), D779.1 (K), D780.1 (K), D781.1 (K), D782.1 (K), D783.1 (K), D784.1 (K), D785.1 (K), D786.1 (K), D787.1 (K), D788.1 (K), D789.1 (K), D790.1 (K), D791.1 (K), D797.2 (A), D815.2 (A), D829.2 (A), D847.2 (A), D861.2 (A), D879.2 (A), D893.2 (A), D911.2 (A), D925.2 (A), D943.2 (A), D957.2 (A), D975.2 (A), D989.2 (A), D1007.2 (A), D1021.2 (A); also elsewhere on the board
/P17: D529.2 (A), D561.2 (A), D593.2 (A), D625.2 (A), D657.2 (A), D689.2 (A), D721.2 (A), D737.1 (K), D738.1 (K), D739.1 (K), D740.1 (K), D741.1 (K), D742.1 (K), D743.1 (K), D744.1 (K), D745.1 (K), D746.1 (K), D747.1 (K), D748.1 (K), D749.1 (K), D750.1 (K), D751.1 (K), D752.1 (K), D753.1 (K), D754.1 (K), D755.1 (K), D756.1 (K), D757.1 (K), D758.1 (K), D759.1 (K), D784.2 (A), D798.2 (A), D816.2 (A), D830.2 (A), D848.2 (A), D862.2 (A), D880.2 (A), D894.2 (A), D912.2 (A), D926.2 (A), D944.2 (A), D958.2 (A), D976.2 (A), D990.2 (A), D1008.2 (A), D1022.2 (A); also elsewhere on the board
/P18: D530.2 (A), D562.2 (A), D594.2 (A), D626.2 (A), D658.2 (A), D690.2 (A), D705.1 (K), D706.1 (K), D707.1 (K), D708.1 (K), D709.1 (K), D710.1 (K), D711.1 (K), D712.1 (K), D713.1 (K), D714.1 (K), D715.1 (K), D716.1 (K), D717.1 (K), D718.1 (K), D719.1 (K), D720.1 (K), D721.1 (K), D722.1 (K), D723.1 (K), D724.1 (K), D725.1 (K), D726.1 (K), D727.1 (K), D753.2 (A), D785.2 (A), D799.2 (A), D817.2 (A), D831.2 (A), D849.2 (A), D863.2 (A), D881.2 (A), D895.2 (A), D913.2 (A), D927.2 (A), D945.2 (A), D959.2 (A), D977.2 (A), D991.2 (A), D1009.2 (A), D1023.2 (A); also elsewhere on the board
/P19: D531.2 (A), D563.2 (A), D595.2 (A), D627.2 (A), D659.2 (A), D673.1 (K), D674.1 (K), D675.1 (K), D676.1 (K), D677.1 (K), D678.1 (K), D679.1 (K), D680.1 (K), D681.1 (K), D682.1 (K), D683.1 (K), D684.1 (K), D685.1 (K), D686.1 (K), D687.1 (K), D688.1 (K), D689.1 (K), D690.1 (K), D691.1 (K), D692.1 (K), D693.1 (K), D694.1 (K), D695.1 (K), D722.2 (A), D754.2 (A), D786.2 (A), D800.2 (A), D818.2 (A), D832.2 (A), D850.2 (A), D864.2 (A), D882.2 (A), D896.2 (A), D914.2 (A), D928.2 (A), D946.2 (A), D960.2 (A), D978.2 (A), D992.2 (A), D1010.2 (A), D1024.2 (A); also elsewhere on the board
/P20: D532.2 (A), D564.2 (A), D596.2 (A), D628.2 (A), D641.1 (K), D642.1 (K), D643.1 (K), D644.1 (K), D645.1 (K), D646.1 (K), D647.1 (K), D648.1 (K), D649.1 (K), D650.1 (K), D651.1 (K), D652.1 (K), D653.1 (K), D654.1 (K), D655.1 (K), D656.1 (K), D657.1 (K), D658.1 (K), D659.1 (K), D660.1 (K), D661.1 (K), D662.1 (K), D663.1 (K), D691.2 (A), D723.2 (A), D755.2 (A), D787.2 (A), D819.2 (A), D851.2 (A), D883.2 (A), D915.2 (A), D947.2 (A), D979.2 (A), D1011.2 (A); also elsewhere on the board
/P21: D533.2 (A), D565.2 (A), D597.2 (A), D609.1 (K), D610.1 (K), D611.1 (K), D612.1 (K), D613.1 (K), D614.1 (K), D615.1 (K), D616.1 (K), D617.1 (K), D618.1 (K), D619.1 (K), D620.1 (K), D621.1 (K), D622.1 (K), D623.1 (K), D624.1 (K), D625.1 (K), D626.1 (K), D627.1 (K), D628.1 (K), D629.1 (K), D630.1 (K), D631.1 (K), D660.2 (A), D692.2 (A), D724.2 (A), D756.2 (A), D788.2 (A), D820.2 (A), D852.2 (A), D884.2 (A), D916.2 (A), D948.2 (A), D980.2 (A), D1012.2 (A); also elsewhere on the board
/P22: D534.2 (A), D566.2 (A), D577.1 (K), D578.1 (K), D579.1 (K), D580.1 (K), D581.1 (K), D582.1 (K), D583.1 (K), D584.1 (K), D585.1 (K), D586.1 (K), D587.1 (K), D588.1 (K), D589.1 (K), D590.1 (K), D591.1 (K), D592.1 (K), D593.1 (K), D594.1 (K), D595.1 (K), D596.1 (K), D597.1 (K), D598.1 (K), D599.1 (K), D629.2 (A), D661.2 (A), D693.2 (A), D725.2 (A), D757.2 (A), D789.2 (A), D821.2 (A), D853.2 (A), D885.2 (A), D917.2 (A), D949.2 (A), D981.2 (A), D1013.2 (A); also elsewhere on the board
/P23: D535.2 (A), D545.1 (K), D546.1 (K), D547.1 (K), D548.1 (K), D549.1 (K), D550.1 (K), D551.1 (K), D552.1 (K), D553.1 (K), D554.1 (K), D555.1 (K), D556.1 (K), D557.1 (K), D558.1 (K), D559.1 (K), D560.1 (K), D561.1 (K), D562.1 (K), D563.1 (K), D564.1 (K), D565.1 (K), D566.1 (K), D567.1 (K), D598.2 (A), D630.2 (A), D662.2 (A), D694.2 (A), D726.2 (A), D758.2 (A), D790.2 (A), D822.2 (A), D854.2 (A), D886.2 (A), D918.2 (A), D950.2 (A), D982.2 (A), D1014.2 (A); also elsewhere on the board
/P24: D513.1 (K), D514.1 (K), D515.1 (K), D516.1 (K), D517.1 (K), D518.1 (K), D519.1 (K), D520.1 (K), D521.1 (K), D522.1 (K), D523.1 (K), D524.1 (K), D525.1 (K), D526.1 (K), D527.1 (K), D528.1 (K), D529.1 (K), D530.1 (K), D531.1 (K), D532.1 (K), D533.1 (K), D534.1 (K), D535.1 (K), D567.2 (A), D599.2 (A), D631.2 (A), D663.2 (A), D695.2 (A), D727.2 (A), D759.2 (A), D791.2 (A), D823.2 (A), D855.2 (A), D887.2 (A), D919.2 (A), D951.2 (A), D983.2 (A), D1015.2 (A); also elsewhere on the board

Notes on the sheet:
There are no diodes at the intersection of rows P1-P8 (inclusive) and columns P20-P24 (inclusive). This accounts for the 40 unused wire pairs mentioned in the other note.
The large grid section seen here is the upper portion of the square charlieplexed network. 24 wires each intersect every other wire at a diode, for a total of 24*23 (552) addressable locations. Not all locations are needed, since the network has 32*16 (512) pixels. There are 552-512=40 unused wire 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
